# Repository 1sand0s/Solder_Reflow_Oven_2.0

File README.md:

# Solder Reflow Oven

<h2> What is it ? </h2>
A homebrew solder reflow oven controller designed around an STM32L053 series MCU with PCB layouting done in Kicad. A solder reflow oven is a device used to 
automatically solder SMD components. When dealing with integrated circuits designed to operate at high frequencies, their packages might not have leads solderable by
hand (leads can add unwanted inductance). Therefore, the only way to solder them is by using a solder reflow oven.  

<h2> How does it work ? </h2>

1. The pads of the PCB are covered in solder paste, typically done with the help of a stencil

2. The components are then carefully placed on the board, the paste helps in providing adhesion to hold the components in place
 
3. The board is then placed inside the oven which controls the ambient temperature to follow a certain profile (specific to the solder paste used)
 
4. During this process the components get soldered onto the board

<h2> Heart of the Solder Reflow Oven </h2>
The heart of the solder reflow oven is the controller (the design included in this repo) which controls the ambient temperature inside the oven to follow the
specified profile. I use PID (Proportional Integrator Differentiator) control to control the ambient temperature.

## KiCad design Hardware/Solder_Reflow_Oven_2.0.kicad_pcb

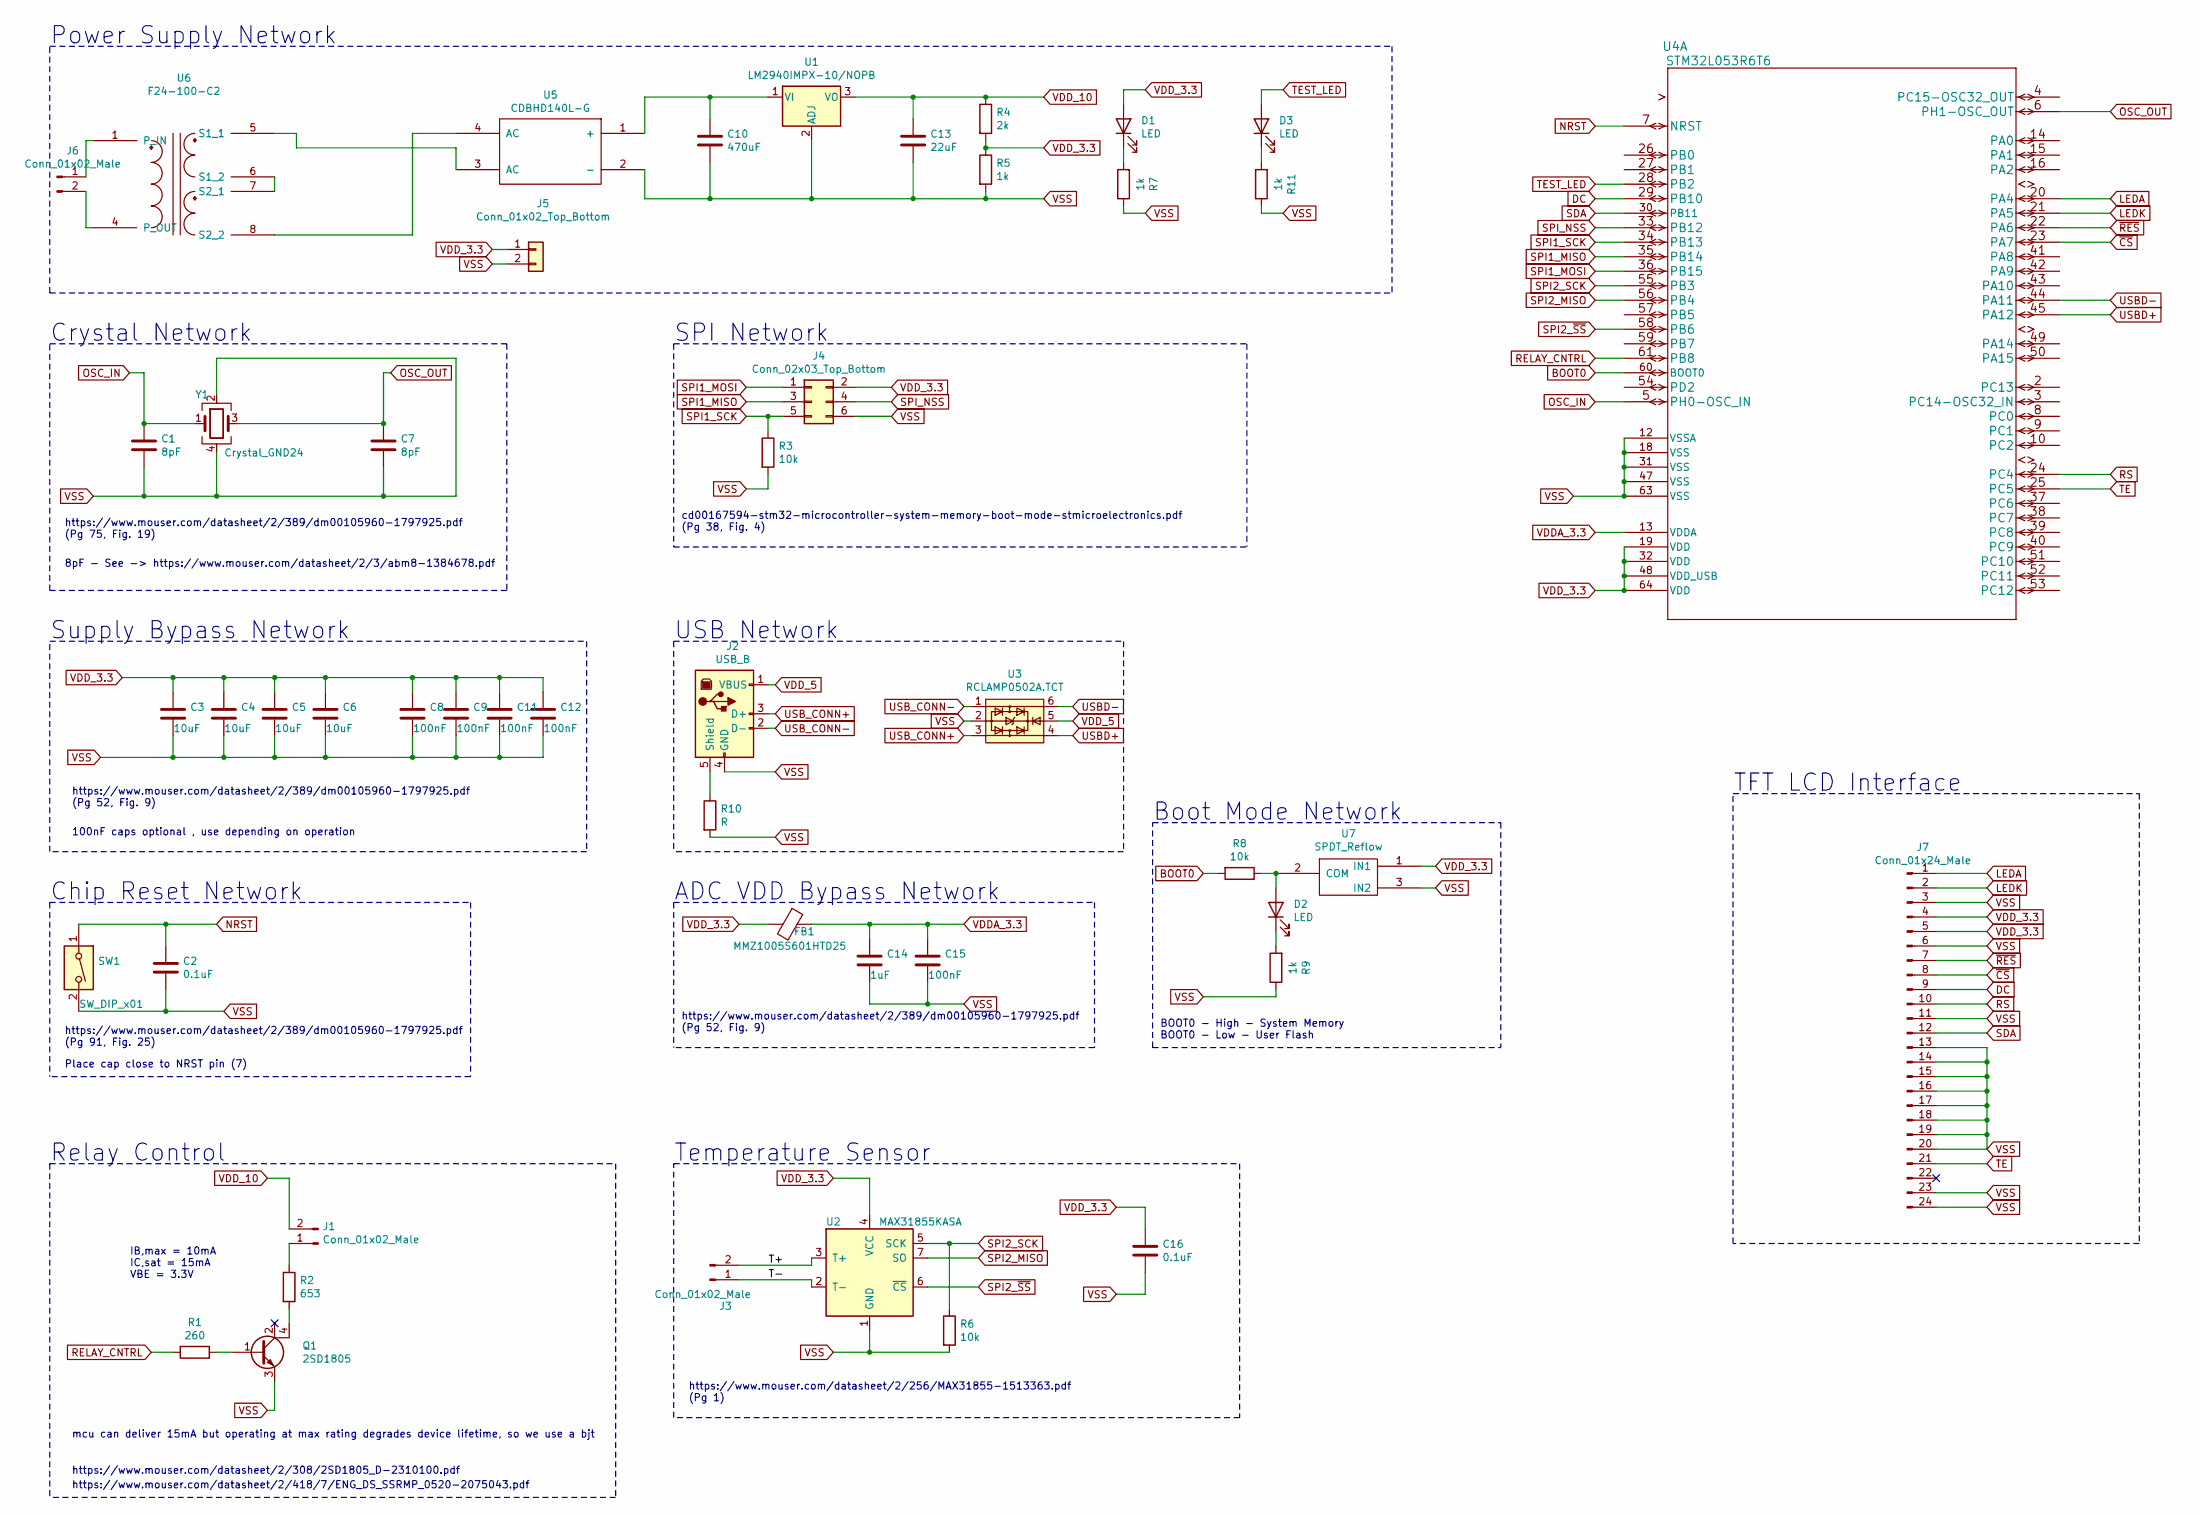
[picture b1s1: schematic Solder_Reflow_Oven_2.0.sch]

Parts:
C1, C7: 8pF; C_0805_2012Metric_Pad1.18x1.45mm_HandSolder
C2, C16: 0.1uF; C_0805_2012Metric_Pad1.18x1.45mm_HandSolder
C3, C4, C5, C6: 10uF; C_0805_2012Metric_Pad1.18x1.45mm_HandSolder
C8, C9, C11, C12, C15: 100nF; C_0805_2012Metric_Pad1.18x1.45mm_HandSolder
C10: 470uF; CP_Radial_D10.0mm_P7.50mm
C13: 22uF; C_0805_2012Metric_Pad1.18x1.45mm_HandSolder
C14: 1uF; C_0805_2012Metric_Pad1.18x1.45mm_HandSolder
D1, D2, D3: LED; LED_0805_2012Metric_Pad1.15x1.40mm_HandSolder
FB1: MMZ1005S601HTD25; L_0805_2012Metric_Pad1.15x1.40mm_HandSolder
J1, J3, J6: Conn_01x02_Male; TerminalBlock_Phoenix_MKDS-1,5-2_1x02_P5.00mm_Horizontal
J2: USB_B; USB_B_Lumberg_2411_02_Horizontal
J4: Conn_02x03_Top_Bottom; PinHeader_2x03_P2.54mm_Vertical
J5: Conn_01x02_Top_Bottom; PinHeader_1x02_P2.54mm_Vertical
J7: Conn_01x24_Male; Hirose_FH12-24S-0.5SH_1x24-1MP_P0.50mm_Horizontal
Q1: 2SD1805; TO-252-3_TabPin4
R1: 260; R_0805_2012Metric_Pad1.20x1.40mm_HandSolder
R2: 653; R_0805_2012Metric_Pad1.20x1.40mm_HandSolder
R3, R6, R8: 10k; R_0805_2012Metric_Pad1.20x1.40mm_HandSolder
R4: 2k; R_0805_2012Metric_Pad1.20x1.40mm_HandSolder
R5, R7, R9, R11: 1k; R_0805_2012Metric_Pad1.20x1.40mm_HandSolder
R10: R; R_0805_2012Metric_Pad1.20x1.40mm_HandSolder
SW1: SW_DIP_x01; SW_Push_1P1T_NO_6x6mm_H9.5mm
U1: LM2940IMPX-10/NOPB; SOT-223
U2: MAX31855KASA; SOIC-8_3.9x4.9mm_P1.27mm
U3: RCLAMP0502A.TCT; SOT-23-6
U4: STM32L053R6T6; LQFP-64_10x10mm_P0.5mm
U5: CDBHD140L-G; TO-269AA
U6: F24-100-C2; Transformer_Breve_TEZ-22x24
U7: SPDT_Reflow
Y1: Crystal_GND24; Crystal_SMD_3225-4Pin_3.2x2.5mm_HandSoldering

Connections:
/T+: J3.2, U2.3 (T+)
/T-: J3.1, U2.2 (T-)
BOOT0: R8.2, U4.60 (BOOT0)
DC: J7.9, U4.29 (PB10)
LEDA: J7.1, U4.20 (PA4)
LEDK: J7.2, U4.21 (PA5)
NRST: C2.1, SW1.1, U4.7 (NRST)
unnamed: C10.1, U1.1 (VI), U5.1 (+)
unnamed: D1.1 (K), R7.2
unnamed: D2.1 (K), R9.2
unnamed: D2.2 (A), R8.1, U7.2 (COM)
unnamed: D3.1 (K), R11.2
unnamed: J1.1, R2.1
unnamed: J2.5 (Shield), R10.1
unnamed: J6.1, U6.1 (P_IN)
unnamed: J6.2, U6.4 (P_OUT)
unnamed: Q1.1 (B), R1.1
unnamed: Q1.4 (C), R2.2
unnamed: D3.2 (A), U4.28 (PB2)
unnamed: U5.3 (AC), U6.5 (S1_1)
unnamed: U5.4 (AC), U6.8 (S2_2)
unnamed: U6.6 (S1_2), U6.7 (S2_1)
OSC_IN: C1.1, U4.5 (PH0-OSC_IN), Y1.1
OSC_OUT: C7.2, U4.6 (PH1-OSC_OUT), Y1.3
RELAY_CNTRL: R1.2, U4.61 (PB8)
RS: J7.10, U4.24 (PC4)
SDA: J7.12, U4.30 (PB11)
SPI1_MISO: J4.3, U4.35 (PB14)
SPI1_MOSI: J4.1, U4.36 (PB15)
SPI1_SCK: J4.5, R3.1, U4.34 (PB13)
SPI2_MISO: U2.7 (SO), U4.56 (PB4)
SPI2_SCK: R6.1, U2.5 (SCK), U4.55 (PB3)
SPI2_~SS: U2.6 (~CS~), U4.58 (PB6)
SPI_NSS: J4.4, U4.33 (PB12)
TE: J7.21, U4.25 (PC5)
USBD+: U3.4, U4.45 (PA12)
USBD-: U3.6, U4.44 (PA11)
USB_CONN+: J2.3 (D+), U3.3
USB_CONN-: J2.2 (D-), U3.1
VDDA_3.3: C14.1, C15.1, FB1.1, U4.13 (VDDA)
VDD_3.3: C3.1, C4.1, C5.1, C6.1, C8.1, C9.1, C11.1, C12.1, C16.1, D1.2 (A), FB1.2, J4.2, J5.1, J7.4, J7.5, R4.2, R5.1, U2.4 (VCC), U4.19 (VDD), U4.32 (VDD), U4.48 (VDD_USB), U4.64 (VDD), U7.1 (IN1)
VDD_5: J2.1 (VBUS), U3.5
VDD_10: C13.1, J1.2, R4.1, U1.3 (VO)
VSS: C1.2, C2.2, C3.2, C4.2, C5.2, C6.2, C7.1, C8.2, C9.2, C10.2, C11.2, C12.2, C13.2, C14.2, C15.2, C16.2, J2.4 (GND), J4.6, J5.2, J7.3, J7.6, J7.11, J7.13, J7.14, J7.15, J7.16, J7.17, J7.18, J7.19, J7.20, J7.23, J7.24, Q1.3 (E), R3.2, R5.2, R6.2, R7.1, R9.1, R10.2, R11.1, SW1.2, U1.2 (ADJ), U2.1 (GND), U3.2, U4.12 (VSSA), U4.18 (VSS), U4.31 (VSS), U4.47 (VSS), U4.63 (VSS), U5.2 (-), U7.3 (IN2), Y1.2, Y1.4
~CS: J7.8, U4.23 (PA7)
~RES: J7.7, U4.22 (PA6)

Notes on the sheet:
https://www.mouser.com/datasheet/2/389/dm00105960-1797925.pdf (Pg 75, Fig. 19)
8pF - See -> https://www.mouser.com/datasheet/2/3/abm8-1384678.pdf
Crystal Network
SPI Network
Supply Bypass Network
100nF caps optional , use depending on operation
https://www.mouser.com/datasheet/2/389/dm00105960-1797925.pdf (Pg 52, Fig. 9)
Place cap close to NRST pin (7)
Chip Reset Network
https://www.mouser.com/datasheet/2/389/dm00105960-1797925.pdf (Pg 91, Fig. 25)
USB Network
ADC VDD Bypass Network
cd00167594-stm32-microcontroller-system-memory-boot-mode-stmicroelectronics.pdf (Pg 38, Fig. 4)
https://www.mouser.com/datasheet/2/308/2SD1805_D-2310100.pdf
Relay Control
IB,max = 10mA IC,sat = 15mA VBE = 3.3V
mcu can deliver 15mA but operating at max rating degrades device lifetime, so we use a bjt
https://www.mouser.com/datasheet/2/418/7/ENG_DS_SSRMP_0520-2075043.pdf
https://www.mouser.com/datasheet/2/256/MAX31855-1513363.pdf (Pg 1)
Temperature Sensor
Power Supply Network
Boot Mode Network
BOOT0 - High - System Memory BOOT0 - Low - User Flash
TFT LCD Interface

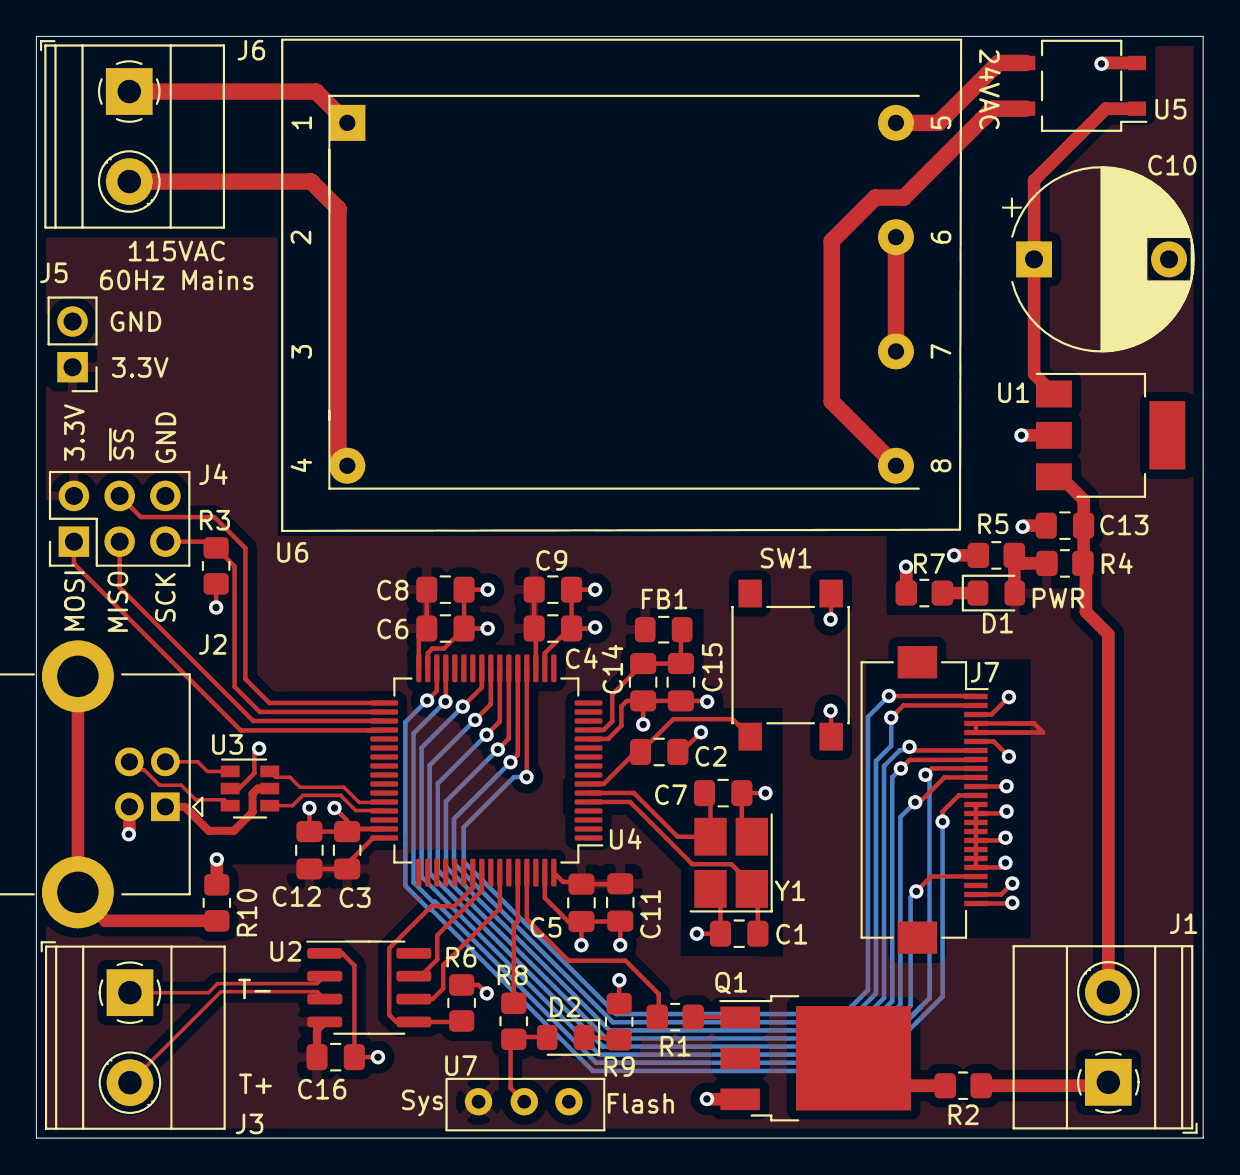
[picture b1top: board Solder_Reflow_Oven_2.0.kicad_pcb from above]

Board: 2 copper layers, 64.8 x 61.2 mm, 46 parts (0 on the bottom side), 44 nets.

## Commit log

2021-11-27 Adding Schematic Files
2021-11-27 Adding schemtic pdf
2021-11-27 Adding BOM
2021-11-28 Adding Fab details
2021-11-29 adding layer pngs
2021-11-29 Updating Readme
2021-12-13 Adding assembled board jpg
2021-12-13 Updating Design for through hole components
2021-12-13 Updating v1.0.0 branch
2021-12-13 adding new gerbers and layout images
2021-12-13 updating schematic pdf
2021-12-13 Adding license badge
2021-12-13 updating readme and versioning
2021-12-13 adding versioning to readme
2021-12-13 updating versioning
2021-12-15 creating branch v1.1.1 for silkscreen readability
2021-12-15 Updating kicad pcb file
2021-12-25 Updating board for version 2.0.0
2021-12-25 Changing 3.3V supply from voltage divider to LDO
2021-12-25 Changing version number in README
2021-12-25 adding support for USART
2021-12-25 Moving to Hardware Folder
2021-12-25 cleaning up
2021-12-26 SPI header position change
2022-01-23 Adding manufactured image
2022-03-07 Updating board to include mounting holes and debugging LED
